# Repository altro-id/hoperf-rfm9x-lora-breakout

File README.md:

# hoperf-rfm9x-lora-breakout
This is a simple breakout board for HopeRF LoRa RFM95/96/97/98W Transceiver.

you could either put SMA or uFL connectors on this board or just simply solder a wire or helical antenna directly.

## Product Preview and Configurations

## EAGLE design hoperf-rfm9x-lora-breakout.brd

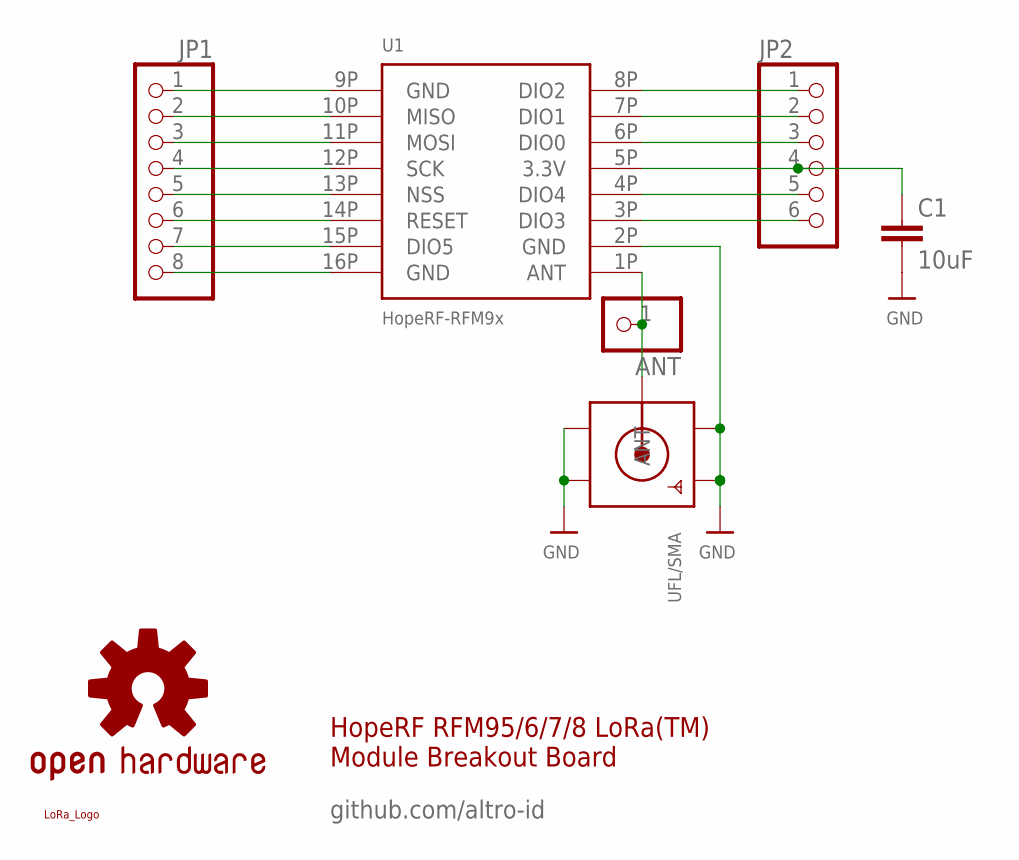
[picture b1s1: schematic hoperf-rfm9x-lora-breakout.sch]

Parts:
ANT: HEADER-1X1ROUND; 1X01_ROUND
C1: 10uF; 0805_MP
JP1: HEADER-1X876MIL; 1X08_ROUND_76
JP2: HEADER-1X676MIL; 1X06_ROUND_76
LOGO1: OSHW-LOGOS; OSHW-LOGO-S
U1: HopeRF-RFM9x; RFM9X_SMT
U$3: LORA_LOGO
UFL/SMA: MICROBUILDER_SMACONNECTOR_EDGE_UFL; MICROBUILDER_SMA_EDGELAUNCH_UFL

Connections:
3.3V: C1.1, JP2.4, U1.5P (3.3V)
DIO0: JP2.3, U1.6P (DIO0)
DIO1: JP2.2, U1.7P (DIO1)
DIO2: JP2.1, U1.8P (DIO2)
DIO3: JP2.6, U1.3P (DIO3)
DIO4: JP2.5, U1.4P (DIO4)
DIO5: JP1.7, U1.15P (DIO5)
GND: C1.2, JP1.1, JP1.8, U1.2P (GND), U1.9P (GND), U1.16P (GND), UFL/SMA.GND@1 (GND1), UFL/SMA.GND@2 (GND2), UFL/SMA.GND@3 (GND3), UFL/SMA.GND@4 (GND4)
MISO: JP1.2, U1.10P (MISO)
MOSI: JP1.3, U1.11P (MOSI)
unnamed: ANT.1, U1.1P (ANT), UFL/SMA.P (ANT)
NSS: JP1.5, U1.13P (NSS)
RESET: JP1.6, U1.14P (RESET)
SCK: JP1.4, U1.12P (SCK)

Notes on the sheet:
HopeRF RFM95/6/7/8 LoRa(TM) Module Breakout Board
github.com/altro-id

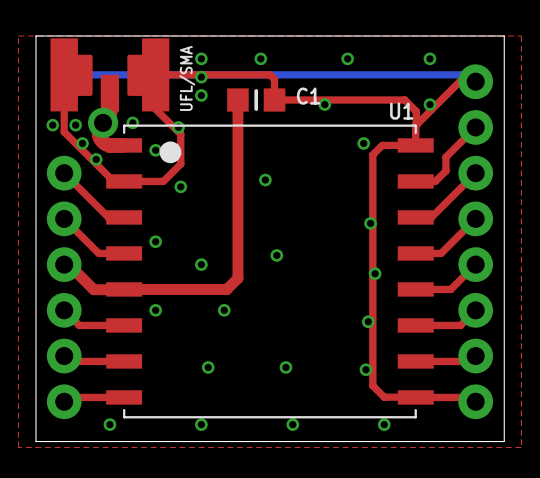
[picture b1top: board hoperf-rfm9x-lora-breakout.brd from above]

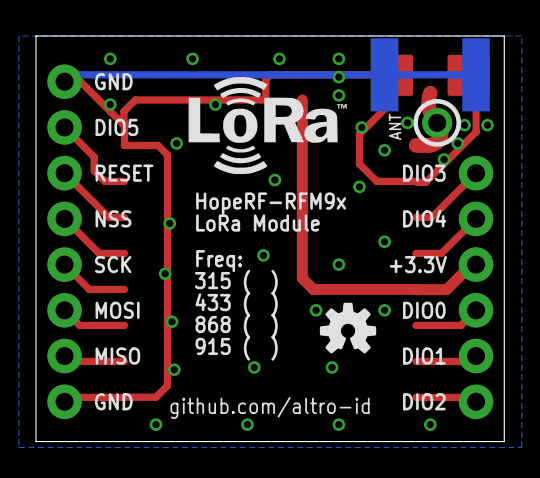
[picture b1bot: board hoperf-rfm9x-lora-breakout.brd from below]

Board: 2 copper layers, 26.0 x 22.5 mm, 8 parts (2 on the bottom side), 14 nets.

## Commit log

2017-09-19 rfm9x lora breakout v1.1

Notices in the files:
parts and their libraries:
microbuilder: This work is placed in the public domain, and may be freely used for commercial and non-commercial work with the following conditions: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
SparkFun-Aesthetics: Licensing: Creative Commons ShareAlike 4.0 International - https://creativecommons.org/licenses/by-sa/4.0
